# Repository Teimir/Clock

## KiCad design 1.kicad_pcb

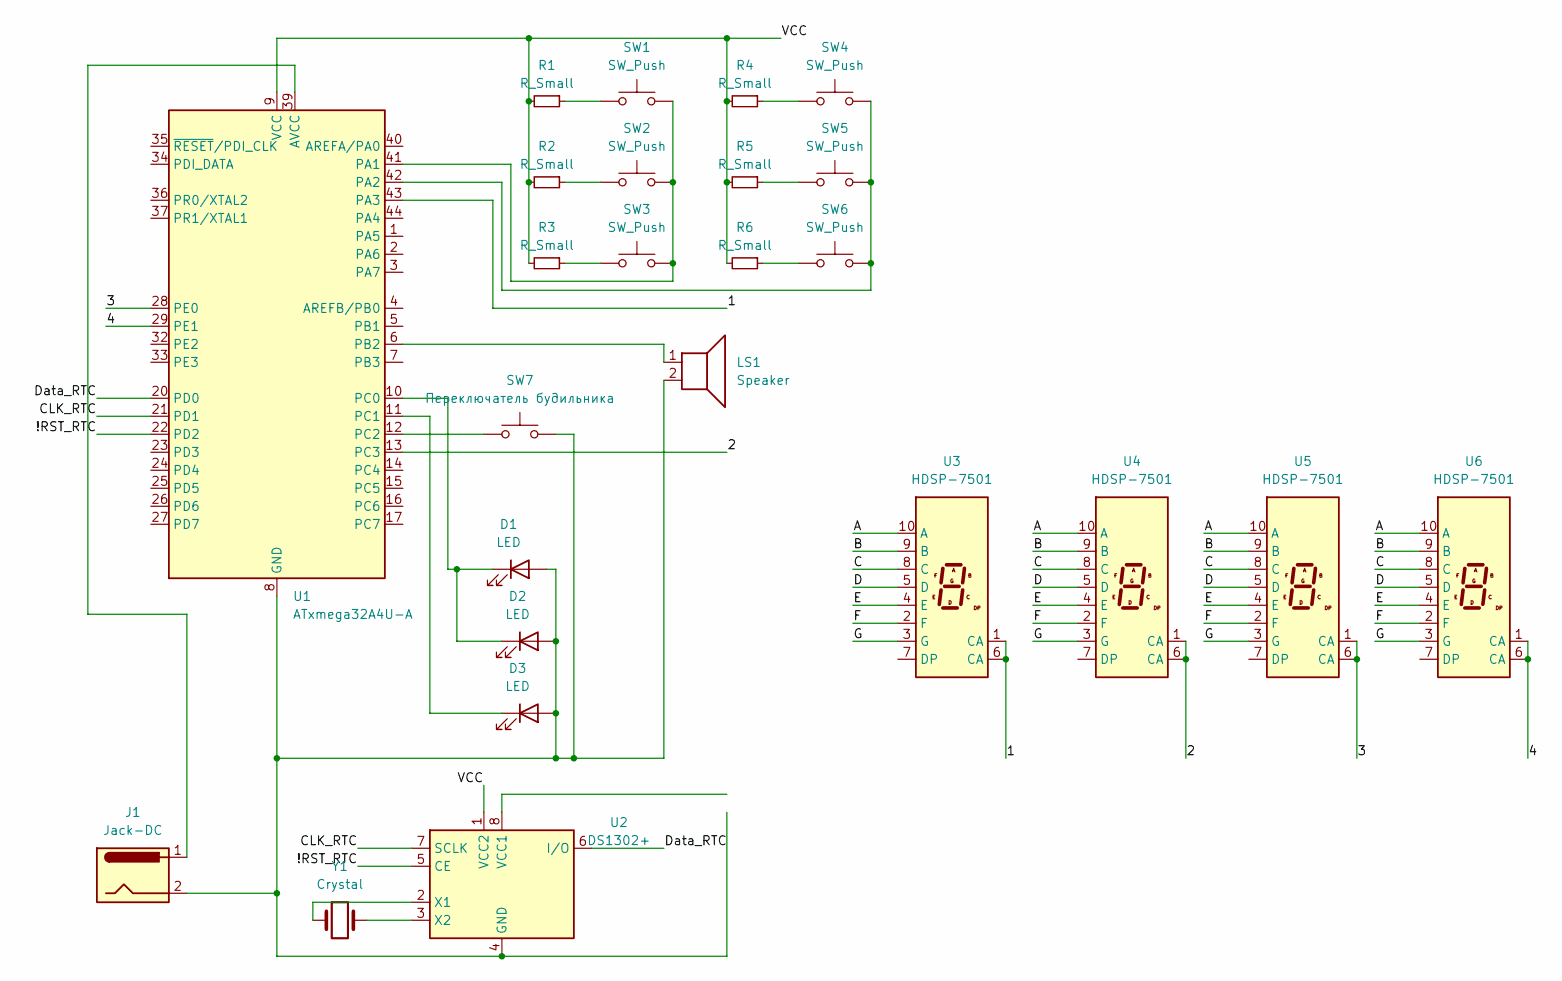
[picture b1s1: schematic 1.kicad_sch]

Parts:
D1, D2, D3: LED; LED_D3.0mm
J1: Jack-DC; BarrelJack_SwitchcraftConxall_RAPC10U_Horizontal
LS1: Speaker
R1, R2, R3, R4, R5, R6: R_Small; R_1206_3216Metric
SW1, SW2, SW3, SW4, SW5, SW6: SW_Push; SW_PUSH_6mm
SW7: Переключатель будильника; SW_PUSH_6mm
U1: ATxmega32A4U-A; TQFP-44_10x10mm_P0.8mm
U2: DS1302+; DIP-8_W7.62mm
U3, U4, U5, U6: HDSP-7501; HDSP-A151
Y1: Crystal

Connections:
/1: U1.43 (PA3), U3.1 (CA), U3.6 (CA)
/2: U1.13 (PC3), U4.1 (CA), U4.6 (CA)
/3: U1.28 (PE0), U5.1 (CA), U5.6 (CA)
/4: U1.29 (PE1), U6.1 (CA), U6.6 (CA)
/!RST_RTC: U1.22 (PD2), U2.5 (CE)
/A: U3.10 (A), U4.10 (A), U5.10 (A), U6.10 (A)
/B: U3.9 (B), U4.9 (B), U5.9 (B), U6.9 (B)
/C: U3.8 (C), U4.8 (C), U5.8 (C), U6.8 (C)
/CLK_RTC: U1.21 (PD1), U2.7 (SCLK)
/D: U3.5 (D), U4.5 (D), U5.5 (D), U6.5 (D)
/Data_RTC: U1.20 (PD0), U2.6 (I/O)
/E: U3.4 (E), U4.4 (E), U5.4 (E), U6.4 (E)
/F: U3.2 (F), U4.2 (F), U5.2 (F), U6.2 (F)
/G: U3.3 (G), U4.3 (G), U5.3 (G), U6.3 (G)
unnamed: D1.2 (A), D2.2 (A), D3.2 (A), J1.2, LS1.2, SW7.2, U1.8 (GND), U1.18 (GND), U1.30 (GND), U1.38 (GND), U2.4 (GND)
unnamed: D1.1 (K), D2.1 (K), U1.10 (PC0)
unnamed: D3.1 (K), U1.11 (PC1)
unnamed: R1.1, SW1.1
unnamed: R2.1, SW2.1
unnamed: R3.1, SW3.1
unnamed: R4.1, SW4.1
unnamed: R5.1, SW5.1
unnamed: R6.1, SW6.1
unnamed: SW1.2, SW2.2, SW3.2, U1.41 (PA1)
unnamed: SW4.2, SW5.2, SW6.2, U1.42 (PA2)
unnamed: LS1.1, U1.6 (PB2)
unnamed: SW7.1, U1.12 (PC2)
unnamed: U2.2 (X1), Y1.1
unnamed: U2.3 (X2), Y1.2

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
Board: 2 copper layers, 27 parts (0 on the bottom side), 27 nets, no tracks yet.

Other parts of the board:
MH1, MH2, MH3, MH4: MountingHole_2.7mm_M2.5_DIN965

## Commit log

2024-02-18 Обновлено
